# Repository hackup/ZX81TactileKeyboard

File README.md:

# ZX81 Tactile Keyboard

This is a PCB for a cheap and easy to build keyboard, designed to go with the [ZX81+38 replica board](https://github.com/mahjongg2/ZX81plus38).

See my [blog post](https://www.hackup.net/2022/01/building-a-new-zx81-computer/) for more details.

## License
[
](http://creativecommons.org/licenses/by-nc-sa/4.0/)

This work is licensed under a
[Creative Commons Attribution-NonCommercial-ShareAlike 4.0 International License](http://creativecommons.org/licenses/by-nc-sa/4.0/).

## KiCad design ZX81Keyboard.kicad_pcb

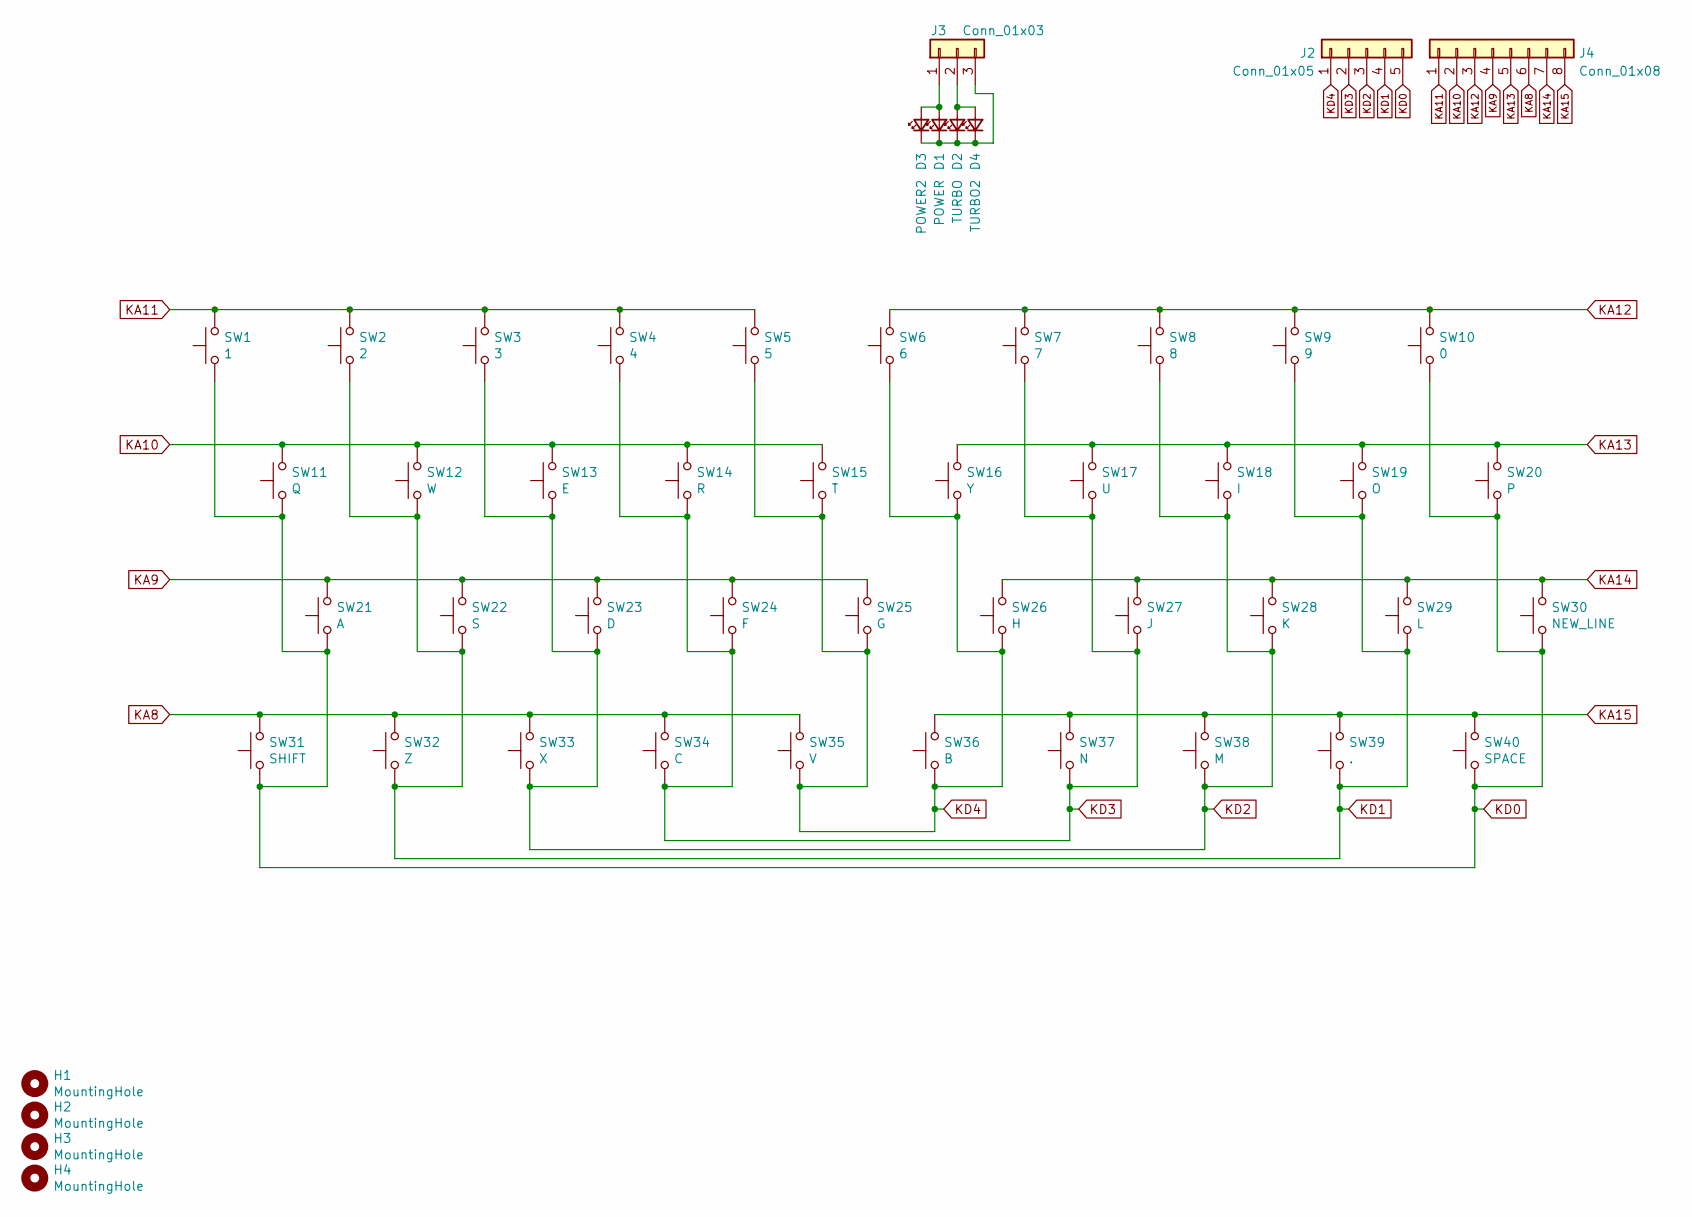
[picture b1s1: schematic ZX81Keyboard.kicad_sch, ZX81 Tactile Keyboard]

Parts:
D1: POWER; LED_D3.0mm
D2: TURBO; LED_D3.0mm
D3: POWER2; LED_0805_2012Metric_Pad1.15x1.40mm_HandSolder
D4: TURBO2; LED_0805_2012Metric_Pad1.15x1.40mm_HandSolder
H1, H2, H3, H4: MountingHole; MountingHole_3.2mm_M3
J2: Conn_01x05; PinHeader_1x05_P2.54mm_Vertical
J3: Conn_01x03; PinHeader_1x03_P2.54mm_Vertical
J4: Conn_01x08; PinHeader_1x08_P2.54mm_Vertical
SW1: 1; SW_PUSH_6mm_H4.3mm
SW2: 2; SW_PUSH_6mm_H4.3mm
SW3: 3; SW_PUSH_6mm_H4.3mm
SW4: 4; SW_PUSH_6mm_H4.3mm
SW5: 5; SW_PUSH_6mm_H4.3mm
SW6: 6; SW_PUSH_6mm_H4.3mm
SW7: 7; SW_PUSH_6mm_H4.3mm
SW8: 8; SW_PUSH_6mm_H4.3mm
SW9: 9; SW_PUSH_6mm_H4.3mm
SW10: 0; SW_PUSH_6mm_H4.3mm
SW11: Q; SW_PUSH_6mm_H4.3mm
SW12: W; SW_PUSH_6mm_H4.3mm
SW13: E; SW_PUSH_6mm_H4.3mm
SW14: R; SW_PUSH_6mm_H4.3mm
SW15: T; SW_PUSH_6mm_H4.3mm
SW16: Y; SW_PUSH_6mm_H4.3mm
SW17: U; SW_PUSH_6mm_H4.3mm
SW18: I; SW_PUSH_6mm_H4.3mm
SW19: O; SW_PUSH_6mm_H4.3mm
SW20: P; SW_PUSH_6mm_H4.3mm
SW21: A; SW_PUSH_6mm_H4.3mm
SW22: S; SW_PUSH_6mm_H4.3mm
SW23: D; SW_PUSH_6mm_H4.3mm
SW24: F; SW_PUSH_6mm_H4.3mm
SW25: G; SW_PUSH_6mm_H4.3mm
SW26: H; SW_PUSH_6mm_H4.3mm
SW27: J; SW_PUSH_6mm_H4.3mm
SW28: K; SW_PUSH_6mm_H4.3mm
SW29: L; SW_PUSH_6mm_H4.3mm
SW30: NEW_LINE; SW_PUSH_6mm_H4.3mm
SW31: SHIFT; SW_PUSH_6mm_H4.3mm
SW32: Z; SW_PUSH_6mm_H4.3mm
SW33: X; SW_PUSH_6mm_H4.3mm
SW34: C; SW_PUSH_6mm_H4.3mm
SW35: V; SW_PUSH_6mm_H4.3mm
SW36: B; SW_PUSH_6mm_H4.3mm
SW37: N; SW_PUSH_6mm_H4.3mm
SW38: M; SW_PUSH_6mm_H4.3mm
SW39: .; SW_PUSH_6mm_H4.3mm
SW40: SPACE; SW_PUSH_6mm_H4.3mm

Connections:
KA8: J4.6, SW31.2, SW32.2, SW33.2, SW34.2, SW35.2
KA9: J4.4, SW21.2, SW22.2, SW23.2, SW24.2, SW25.2
KA10: J4.2, SW11.2, SW12.2, SW13.2, SW14.2, SW15.2
KA11: J4.1, SW1.2, SW2.2, SW3.2, SW4.2, SW5.2
KA12: J4.3, SW6.2, SW7.2, SW8.2, SW9.2, SW10.2
KA13: J4.5, SW16.2, SW17.2, SW18.2, SW19.2, SW20.2
KA14: J4.7, SW26.2, SW27.2, SW28.2, SW29.2, SW30.2
KA15: J4.8, SW36.2, SW37.2, SW38.2, SW39.2, SW40.2
KD0: J2.5, SW1.1, SW10.1, SW11.1, SW20.1, SW21.1, SW30.1, SW31.1, SW40.1
KD1: J2.4, SW2.1, SW9.1, SW12.1, SW19.1, SW22.1, SW29.1, SW32.1, SW39.1
KD2: J2.3, SW3.1, SW8.1, SW13.1, SW18.1, SW23.1, SW28.1, SW33.1, SW38.1
KD3: J2.2, SW4.1, SW7.1, SW14.1, SW17.1, SW24.1, SW27.1, SW34.1, SW37.1
KD4: J2.1, SW5.1, SW6.1, SW15.1, SW16.1, SW25.1, SW26.1, SW35.1, SW36.1
unnamed: D1.2 (A), D3.2 (A), J3.1
unnamed: D1.1 (K), D2.1 (K), D3.1 (K), D4.1 (K), J3.3
unnamed: D2.2 (A), D4.2 (A), J3.2

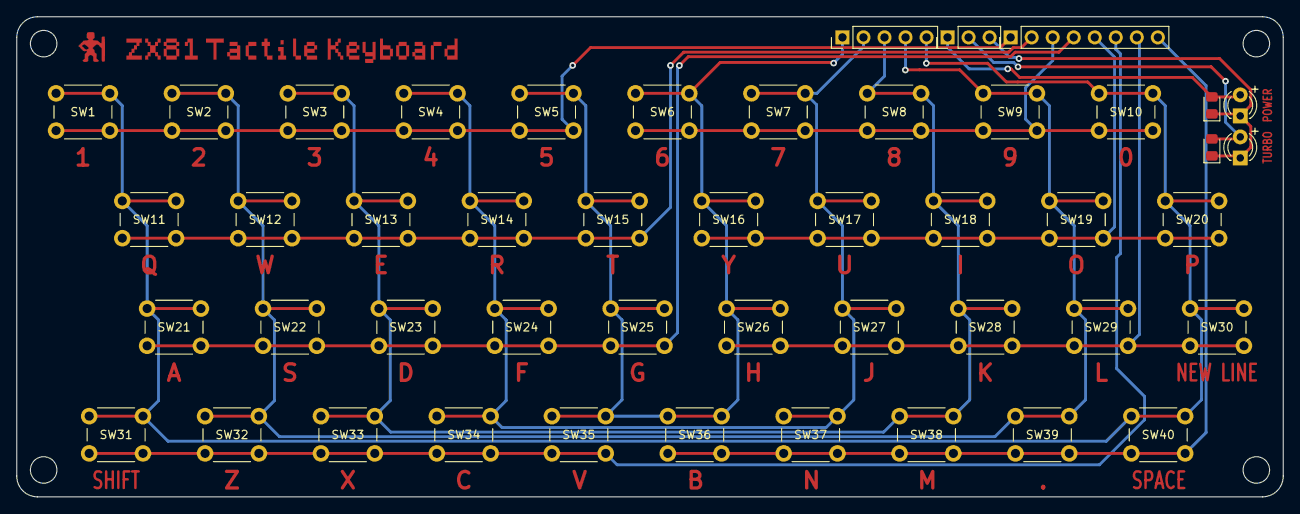
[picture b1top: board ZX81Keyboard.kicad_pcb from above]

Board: 2 copper layers, 153.0 x 58.0 mm, 51 parts (0 on the bottom side), 16 nets.

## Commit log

2021-11-14 Initial commit.
2021-11-14 Nearing completion.
2021-11-24 Fixed connector orientation.
2022-02-06 Preparing for release.
2022-02-06 Added keyboard cover design file.
2023-08-29 Converted to KiCAD 7 file formats.
2023-08-29 Rotated connector back again to better accommodate rev. 1.9 of the motherboard.
